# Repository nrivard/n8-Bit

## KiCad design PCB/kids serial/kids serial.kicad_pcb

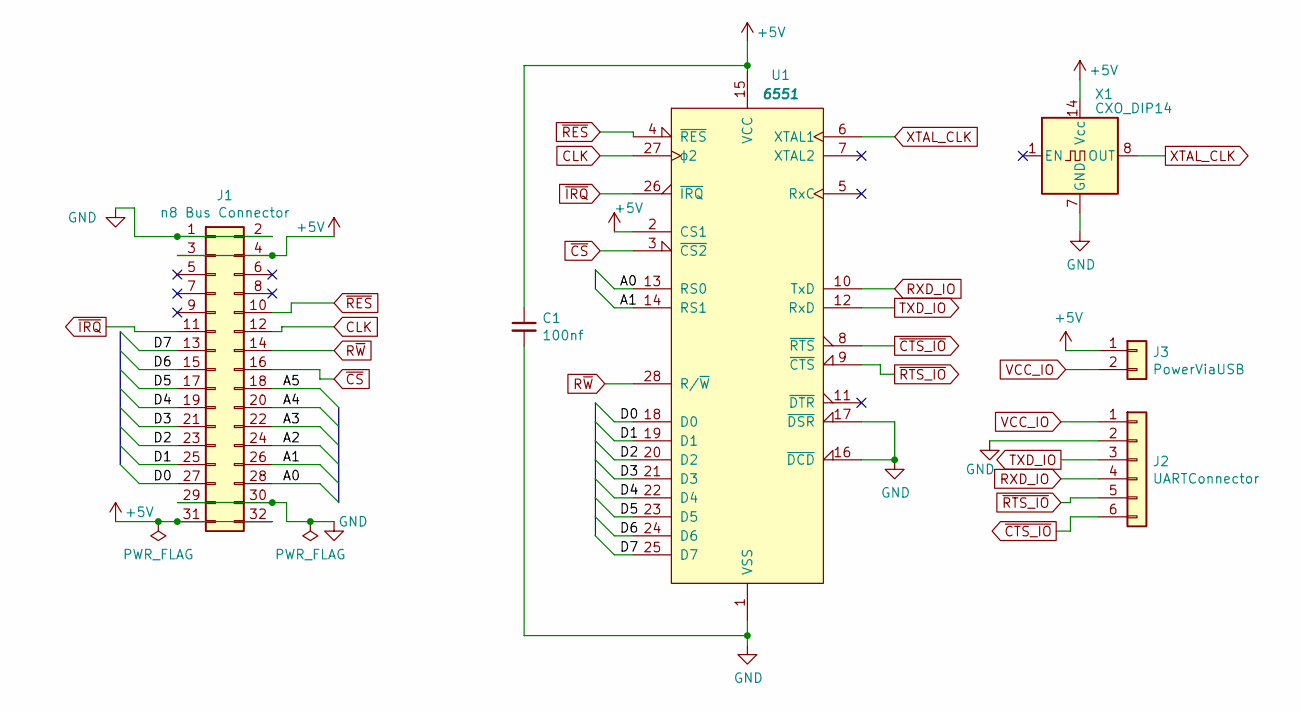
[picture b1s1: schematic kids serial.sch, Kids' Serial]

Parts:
C1: 100nf; C_Disc_D5.0mm_W2.5mm_P2.50mm
J1: n8 Bus Connector; PinHeader_2x16_P2.54mm_Horizontal
J2: UARTConnector; PinSocket_1x06_P2.54mm_Horizontal
J3: PowerViaUSB; PinHeader_1x02_P2.54mm_Vertical
U1: 6551; DIP-28_W15.24mm_Socket
X1: CXO_DIP14; Oscillator_DIP-14

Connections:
+5V: C1.1, J1.3, J1.4, J1.31, J1.32, J3.1, U1.2 (CS1), U1.15 (VCC), X1.14 (Vcc)
/A0: J1.28, U1.13 (RS0)
/A1: J1.26, U1.14 (RS1)
/A2: J1.24
/A3: J1.22
/A4: J1.20
/A5: J1.18
/D0: J1.27, U1.18 (D0)
/D1: J1.25, U1.19 (D1)
/D2: J1.23, U1.20 (D2)
/D3: J1.21, U1.21 (D3)
/D4: J1.19, U1.22 (D4)
/D5: J1.17, U1.23 (D5)
/D6: J1.15, U1.24 (D6)
/D7: J1.13, U1.25 (D7)
CLK: J1.12, U1.27 (ϕ2)
GND: C1.2, J1.1, J1.2, J1.29, J1.30, J2.2, U1.1 (VSS), U1.16 (~DCD), U1.17 (~DSR), X1.7 (GND)
RXD_IO: J2.4, U1.10 (TxD)
R~W: J1.14, U1.28 (R/~W)
TXD_IO: J2.3, U1.12 (RxD)
VCC_IO: J2.1, J3.2
XTAL_CLK: U1.6 (XTAL1), X1.8 (OUT)
~CS: J1.16, U1.3 (~CS2)
~CTS_IO: J2.6, U1.8 (~RTS)
~IRQ: J1.11, U1.26 (~IRQ)
~RES: J1.10, U1.4 (~RES)
~RTS_IO: J2.5, U1.9 (~CTS)

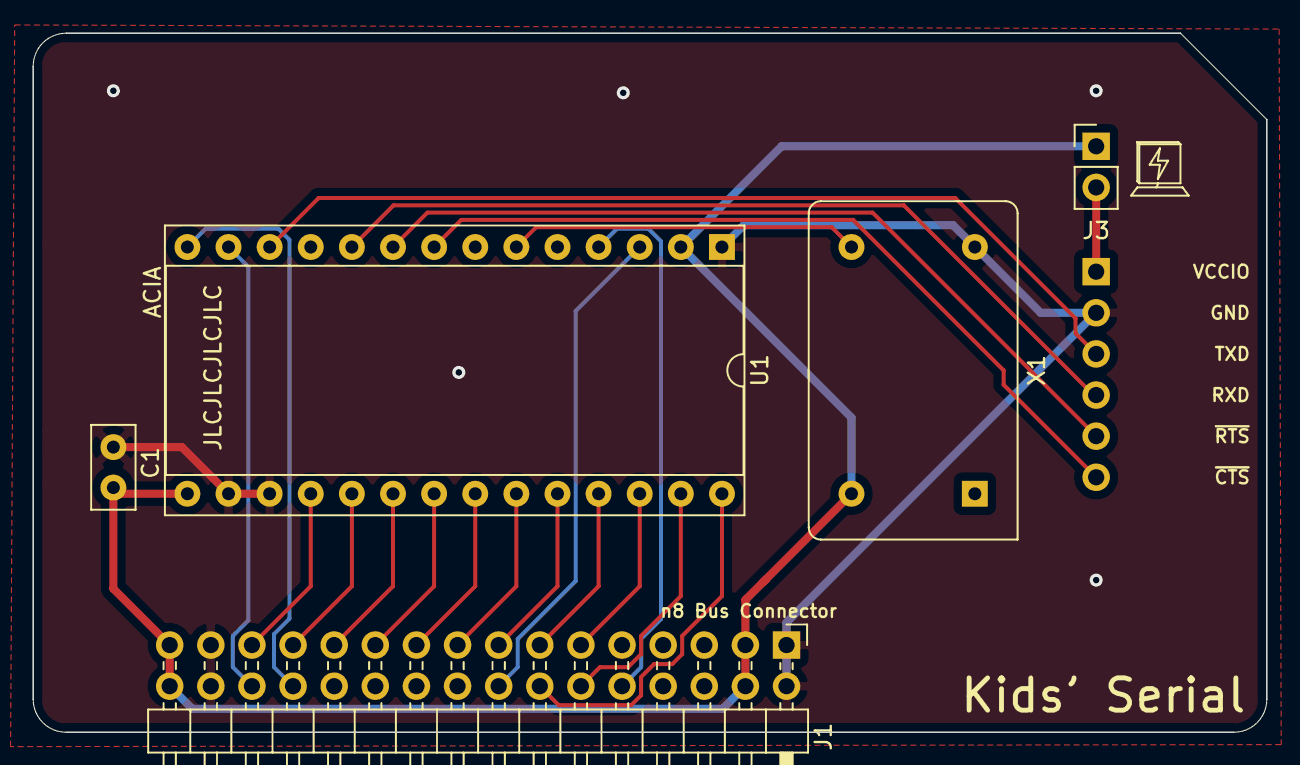
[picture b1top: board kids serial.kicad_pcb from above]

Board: 2 copper layers, 76.2 x 43.2 mm, 6 parts (1 on the bottom side), 23 nets.

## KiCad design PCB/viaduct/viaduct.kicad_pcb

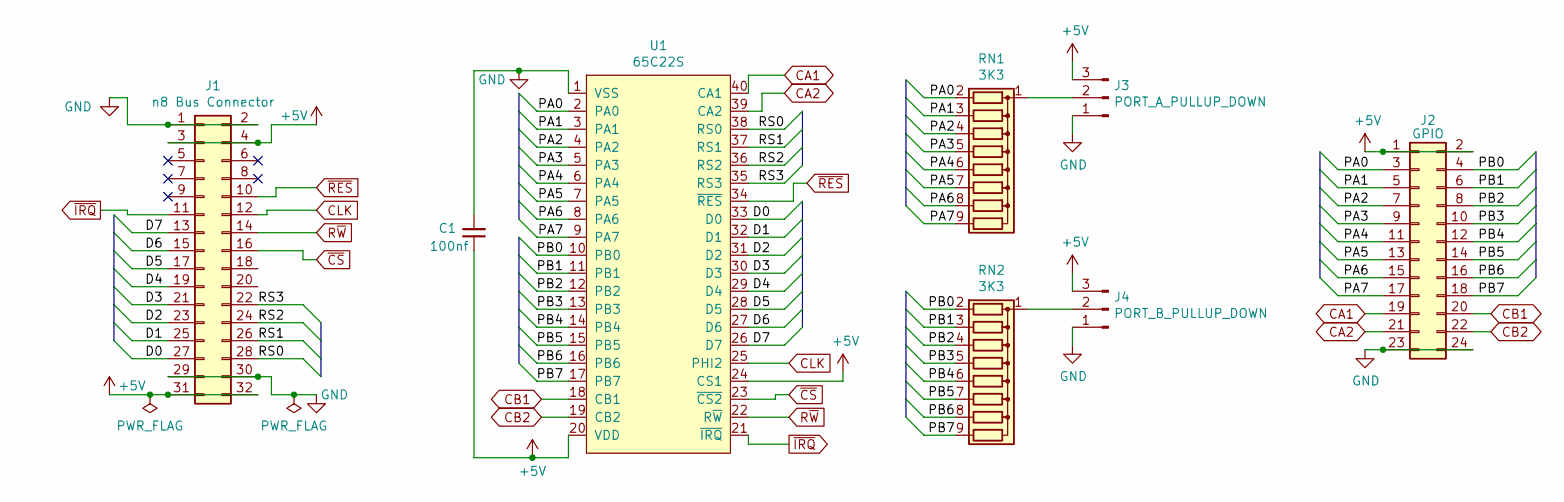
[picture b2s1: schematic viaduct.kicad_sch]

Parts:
C1: 100nf; C_Disc_D5.0mm_W2.5mm_P2.50mm
J1: n8 Bus Connector; PinHeader_2x16_P2.54mm_Horizontal
J2: GPIO; PinSocket_2x12_P2.54mm_Horizontal
J3: PORT_A_PULLUP_DOWN; PinHeader_1x03_P2.54mm_Vertical
J4: PORT_B_PULLUP_DOWN; PinHeader_1x03_P2.54mm_Vertical
RN1, RN2: 3K3; R_Array_SIP9
U1: 65C22S; DIP-40_W15.24mm_Socket

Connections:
+5V: C1.1, J1.3, J1.4, J1.31, J1.32, J2.1, J2.2, J3.3, J4.3, U1.20 (VDD), U1.24 (CS1)
/D0: J1.27, U1.33 (D0)
/D1: J1.25, U1.32 (D1)
/D2: J1.23, U1.31 (D2)
/D3: J1.21, U1.30 (D3)
/D4: J1.19, U1.29 (D4)
/D5: J1.17, U1.28 (D5)
/D6: J1.15, U1.27 (D6)
/D7: J1.13, U1.26 (D7)
/PA0: J2.3, RN1.2 (R1), U1.2 (PA0)
/PA1: J2.5, RN1.3 (R2), U1.3 (PA1)
/PA2: J2.7, RN1.4 (R3), U1.4 (PA2)
/PA3: J2.9, RN1.5 (R4), U1.5 (PA3)
/PA4: J2.11, RN1.6 (R5), U1.6 (PA4)
/PA5: J2.13, RN1.7 (R6), U1.7 (PA5)
/PA6: J2.15, RN1.8 (R7), U1.8 (PA6)
/PA7: J2.17, RN1.9 (R8), U1.9 (PA7)
/PB0: J2.4, RN2.2 (R1), U1.10 (PB0)
/PB1: J2.6, RN2.3 (R2), U1.11 (PB1)
/PB2: J2.8, RN2.4 (R3), U1.12 (PB2)
/PB3: J2.10, RN2.5 (R4), U1.13 (PB3)
/PB4: J2.12, RN2.6 (R5), U1.14 (PB4)
/PB5: J2.14, RN2.7 (R6), U1.15 (PB5)
/PB6: J2.16, RN2.8 (R7), U1.16 (PB6)
/PB7: J2.18, RN2.9 (R8), U1.17 (PB7)
/RS0: J1.28, U1.38 (RS0)
/RS1: J1.26, U1.37 (RS1)
/RS2: J1.24, U1.36 (RS2)
/RS3: J1.22, U1.35 (RS3)
CA1: J2.19, U1.40 (CA1)
CA2: J2.21, U1.39 (CA2)
CB1: J2.20, U1.18 (CB1)
CB2: J2.22, U1.19 (CB2)
CLK: J1.12, U1.25 (PHI2)
GND: C1.2, J1.1, J1.2, J1.29, J1.30, J2.23, J2.24, J3.1, J4.1, U1.1 (VSS)
unnamed: J3.2, RN1.1 (common)
unnamed: J4.2, RN2.1 (common)
R~W: J1.14, U1.22 (R~W)
~CS: J1.16, U1.23 (~CS2)
~IRQ: J1.11, U1.21 (~IRQ)
~RES: J1.10, U1.34 (~RES)

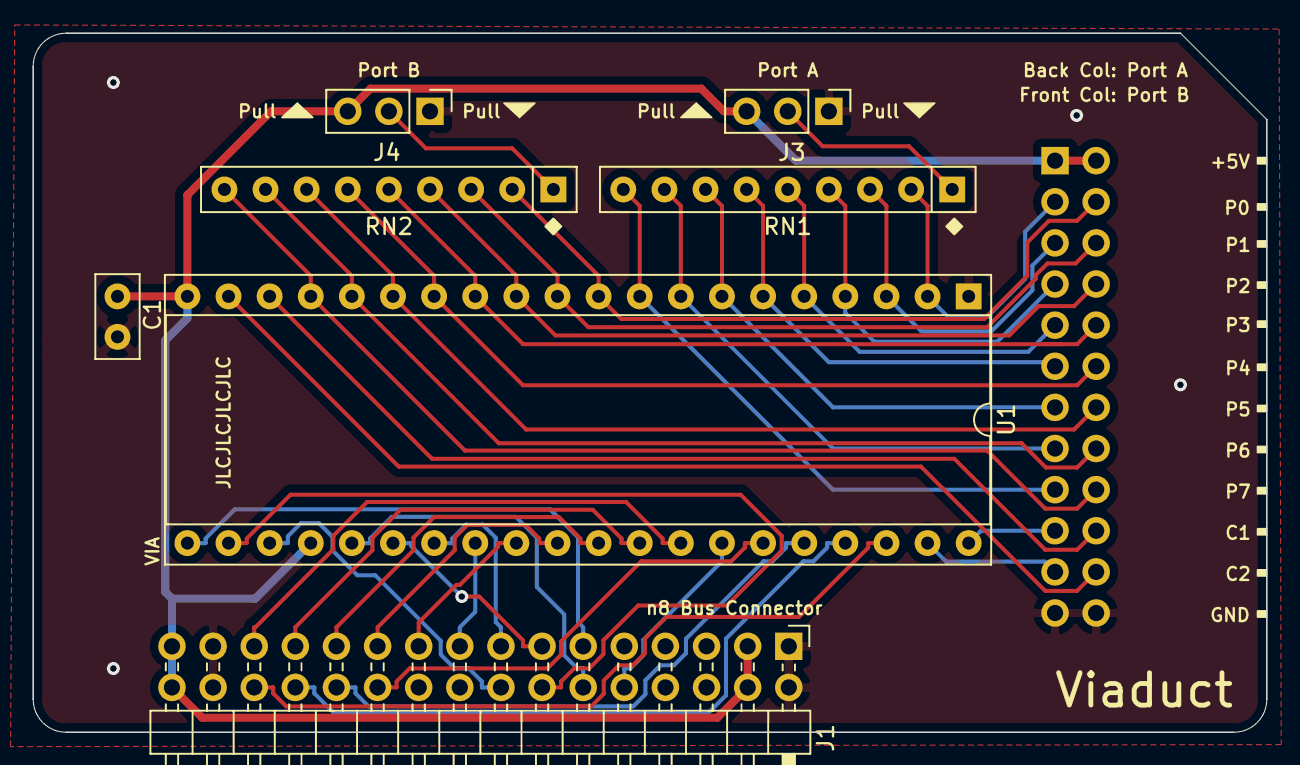
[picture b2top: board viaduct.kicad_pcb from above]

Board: 2 copper layers, 76.2 x 43.2 mm, 8 parts (1 on the bottom side), 41 nets.
